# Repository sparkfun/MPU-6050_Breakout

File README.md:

Triple Axis Accelerometer & Gyro Breakout - MPU-6050
====================================================
[  
*Triple Axis Accelerometer & Gyro Breakout-MPU-6050 (SEN-11028)*](https://www.sparkfun.com/products/11028)

The MPU-6050 combines a 3-axis MEMS gyroscope and 3-axis accelerometer onto a single IC. Our breakout board
allows I2C access for the data from these sensors. 

Repository Contents
-------------------
* **/Hardware** - All Eagle design files (.brd, .sch)
* **/Production** - Test bed files and production panel files

License Information
-------------------
The hardware is released under [Creative Commons Share-alike 3.0](http://creativecommons.org/licenses/by-sa/3.0/).

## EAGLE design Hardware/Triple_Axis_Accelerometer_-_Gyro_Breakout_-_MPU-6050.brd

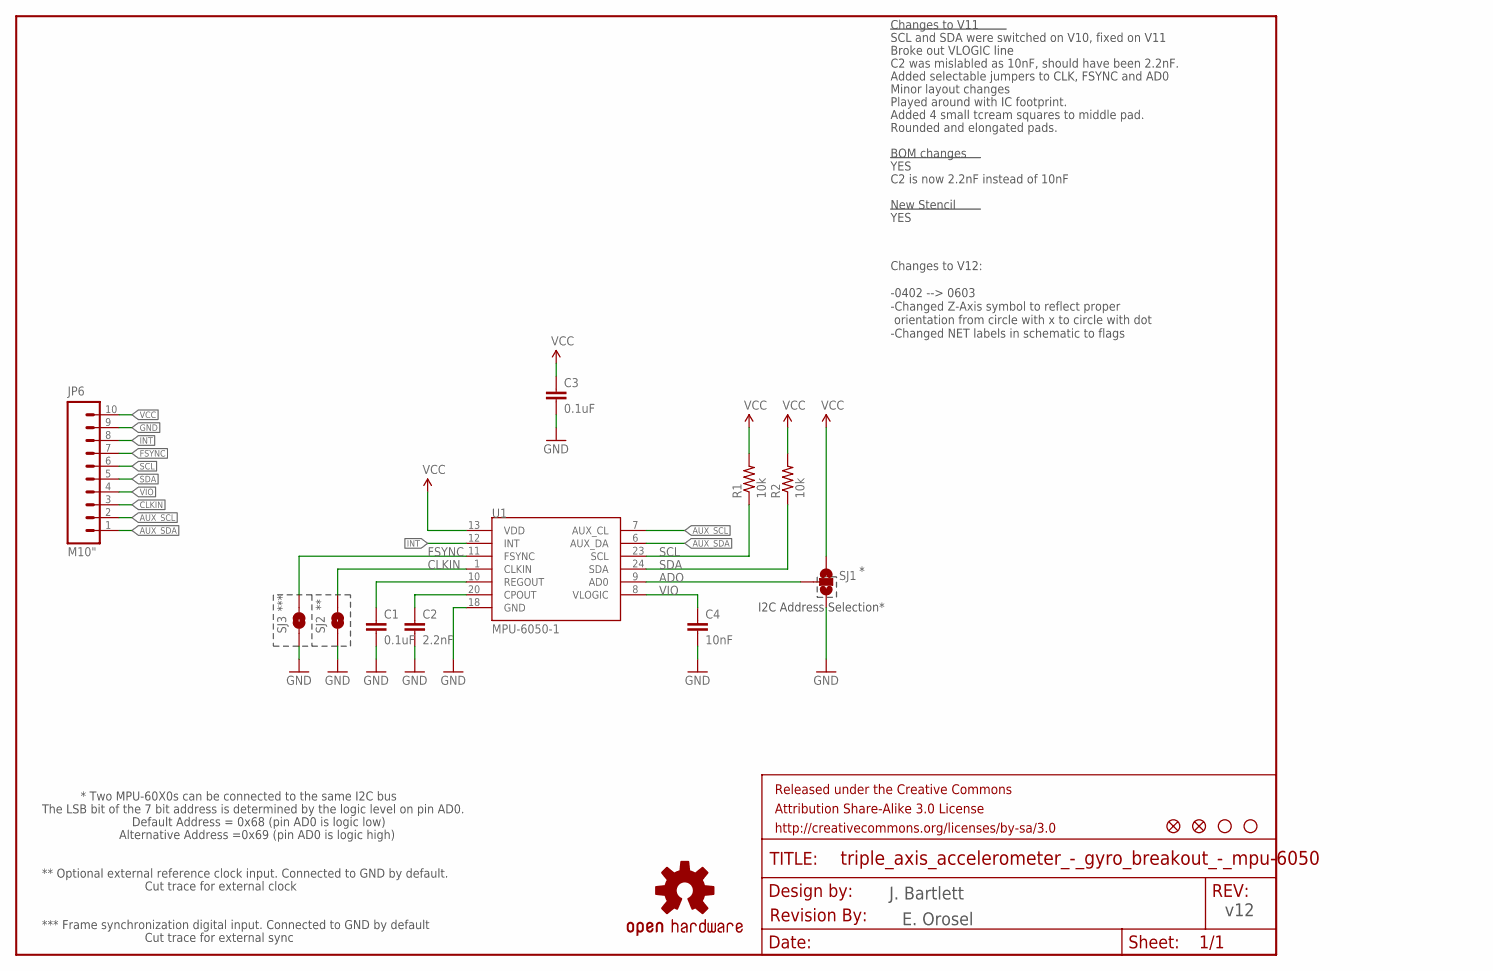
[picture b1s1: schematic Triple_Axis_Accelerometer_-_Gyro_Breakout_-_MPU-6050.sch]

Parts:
C1, C3: 0.1uF; 0603-CAP
C2: 2.2nF; 0603-CAP
C4: 10nF; 0603-CAP
FRAME1: FRAME-LETTER; CREATIVE_COMMONS
JP2, JP5: FIDUCIALUFIDUCIAL; MICRO-FIDUCIAL
JP3, JP4: STAND-OFFTIGHT; STAND-OFF-TIGHT
JP6: M10"; 1X10
R1, R2: 10k; 0603-RES
SJ1: SOLDERJUMPER_2WAYPASTE2&3; SJ_3_PASTE2&3
SJ2, SJ3: SOLDERJUMPERTRACE; SJ_2S-TRACE
U1: MPU-6050-1; QFN-24-4MM2
U$1: OSHW-LOGOS; OSHW-LOGO-S
U$5: REVISION

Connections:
ADO: SJ1.2, U1.9 (AD0)
AUX_SCL: JP6.2, U1.7 (AUX_CL)
AUX_SDA: JP6.1, U1.6 (AUX_DA)
CLKIN: JP6.3, SJ2.2, U1.1 (CLKIN)
FSYNC: JP6.7, SJ3.2, U1.11 (FSYNC)
GND: C1.2, C2.2, C3.2, C4.2, JP6.9, SJ1.3, SJ2.1, SJ3.1, U1.18 (GND)
INT: JP6.8, U1.12 (INT)
unnamed: C2.1, U1.20 (CPOUT)
unnamed: C1.1, U1.10 (REGOUT)
SCL: JP6.6, R1.1, U1.23 (SCL)
SDA: JP6.5, R2.1, U1.24 (SDA)
VCC: C3.1, JP6.10, R1.2, R2.2, SJ1.1, U1.13 (VDD)
VIO: C4.1, JP6.4, U1.8 (VLOGIC)

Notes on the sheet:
J. Bartlett
I2C Address Selection*
*** Frame synchronization digital input. Connected to GND by default
***
Cut trace for external sync
* Two MPU-60X0s can be connected to the same I2C bus
Default Address = 0x68 (pin AD0 is logic low)
Alternative Address =0x69 (pin AD0 is logic high)
The LSB bit of the 7 bit address is determined by the logic level on pin AD0.
** Optional external reference clock input. Connected to GND by default.
Cut trace for external clock
Changes to V11
SCL and SDA were switched on V10, fixed on V11
C2 was mislabled as 10nF, should have been 2.2nF.
Broke out VLOGIC line
BOM changes
New Stencil
YES
C2 is now 2.2nF instead of 10nF
Minor layout changes
Added selectable jumpers to CLK, FSYNC and AD0
Played around with IC footprint.
Changes to V12: -0402 --> 0603 -Changed Z-Axis symbol to reflect proper orientation from circle with x to circle with dot -Changed NET labels in schematic to flags
E. Orosel
v12
Added 4 small tcream squares to middle pad.
Rounded and elongated pads.

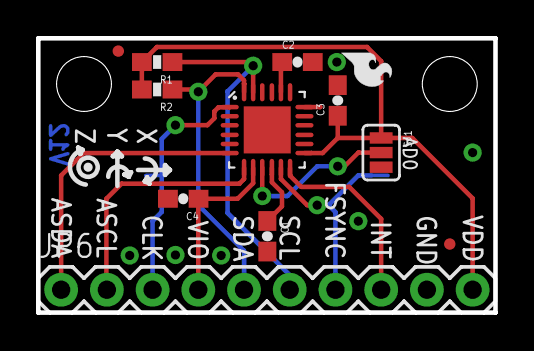
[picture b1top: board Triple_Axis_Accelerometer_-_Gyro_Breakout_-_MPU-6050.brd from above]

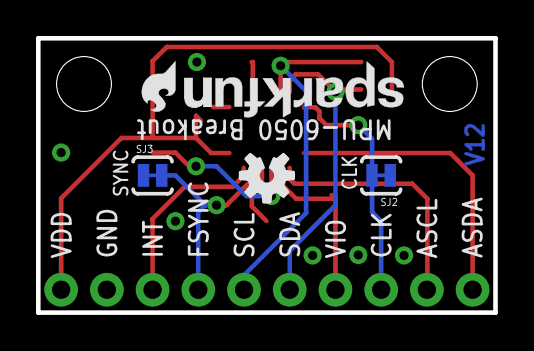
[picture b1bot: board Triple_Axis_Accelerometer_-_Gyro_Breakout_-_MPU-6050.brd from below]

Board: 2 copper layers, 25.4 x 15.2 mm, 21 parts (5 on the bottom side), 13 nets.

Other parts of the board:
U$2, U$3: SFE-LOGO-FLAME
U$4: SFE-NEW-WEB

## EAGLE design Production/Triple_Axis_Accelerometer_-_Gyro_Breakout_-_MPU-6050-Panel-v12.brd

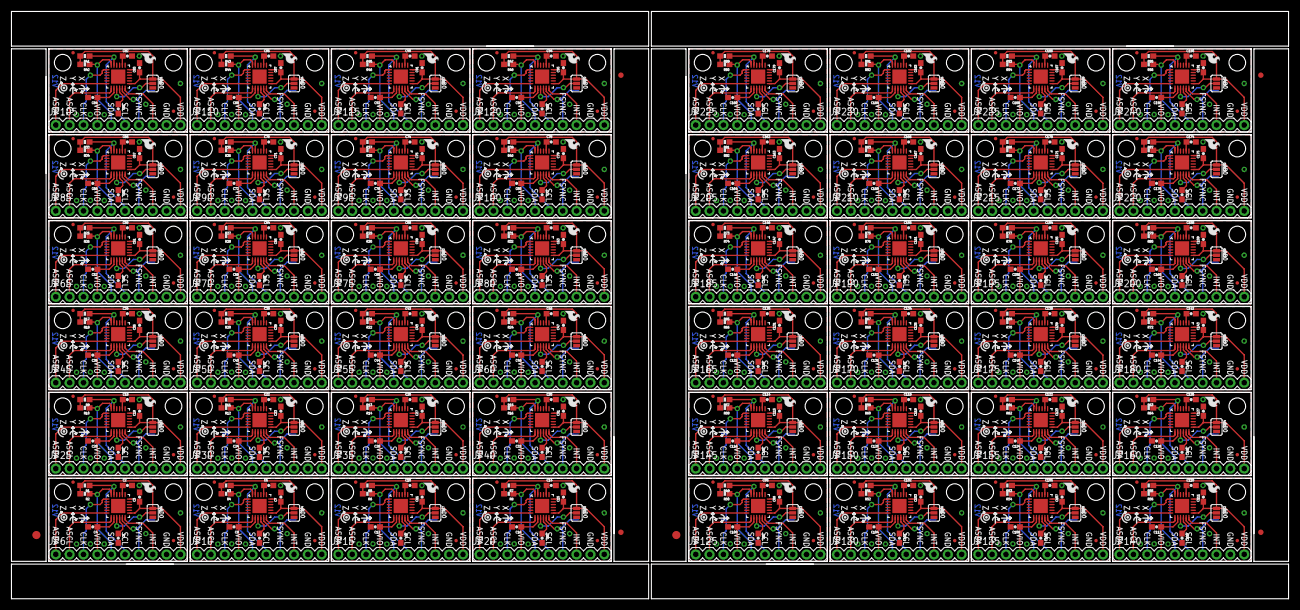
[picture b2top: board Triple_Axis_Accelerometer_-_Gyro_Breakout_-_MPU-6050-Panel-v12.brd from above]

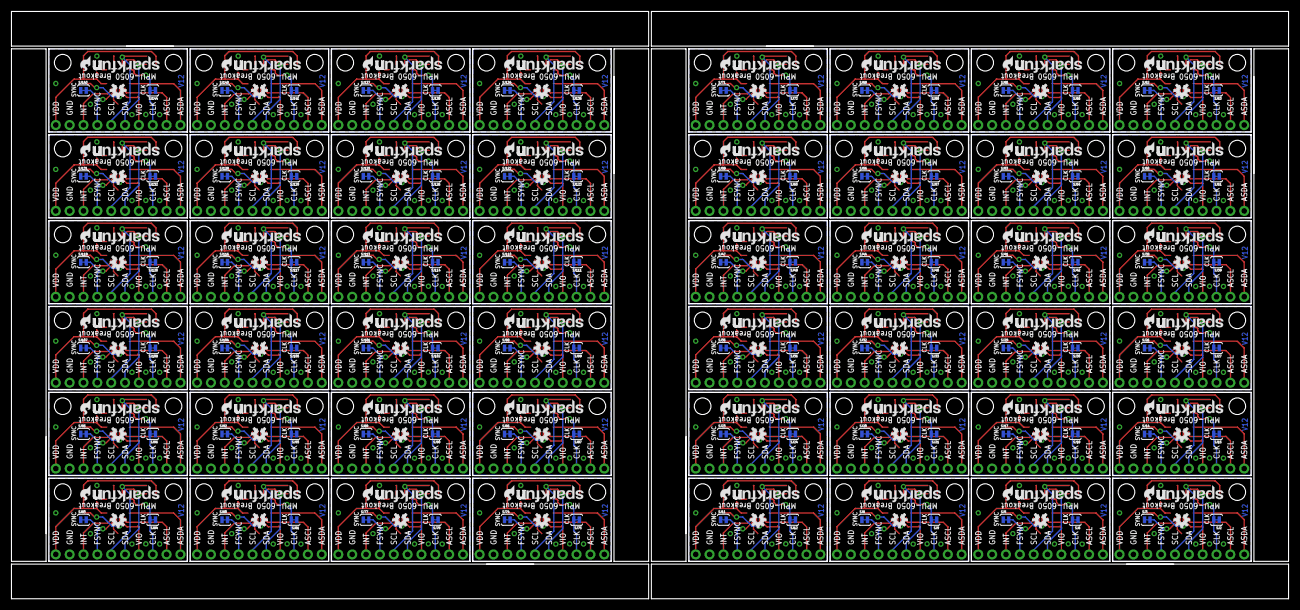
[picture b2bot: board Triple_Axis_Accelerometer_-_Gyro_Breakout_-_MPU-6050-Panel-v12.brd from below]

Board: 2 copper layers, 234.2 x 107.7 mm, 918 parts (240 on the bottom side), 624 nets.

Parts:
C1, C3, C5, C7, C9, C11, C13, C15, C17, C19, C21, C23, C25, C27, C29, C31, C33, C35, C37, C39, C41, C43, C45, C47, C49, C51, C53, C55, C57, C59, C61, C63, C65, C67, C69, C71, C73, C75, C77, C79, C81, C83, C85, C87, C89, C91, C93, C95, C97, C99, C101, C103, C105, C107, C109, C111, C113, C115, C117, C119, C121, C123, C125, C127, C129, C131, C133, C135, C137, C139, C141, C143, C145, C147, C149, C151, C153, C155, C157, C159, C161, C163, C165, C167, C169, C171, C173, C175, C177, C179, C181, C183, C185, C187, C189, C191: 0.1uF; 0603-CAP
C2, C6, C10, C14, C18, C22, C26, C30, C34, C38, C42, C46, C50, C54, C58, C62, C66, C70, C74, C78, C82, C86, C90, C94, C98, C102, C106, C110, C114, C118, C122, C126, C130, C134, C138, C142, C146, C150, C154, C158, C162, C166, C170, C174, C178, C182, C186, C190: 2.2nF; 0603-CAP
C4, C8, C12, C16, C20, C24, C28, C32, C36, C40, C44, C48, C52, C56, C60, C64, C68, C72, C76, C80, C84, C88, C92, C96, C100, C104, C108, C112, C116, C120, C124, C128, C132, C136, C140, C144, C148, C152, C156, C160, C164, C168, C172, C176, C180, C184, C188, C192: 10nF; 0603-CAP
E$1, E$6: FIDUCIAL-1.5X3
E$2, E$3, E$4, E$5: FIDUCIAL-1X2
JP1, JP3, JP4, JP7, JP11, JP12, JP16, JP17, JP21, JP22, JP26, JP27, JP31, JP32, JP36, JP37, JP41, JP42, JP46, JP47, JP51, JP52, JP56, JP57, JP61, JP62, JP66, JP67, JP71, JP72, JP76, JP77, JP81, JP82, JP86, JP87, JP91, JP92, JP96, JP97, JP101, JP102, JP106, JP107, JP111, JP112, JP116, JP117, JP121, JP122, JP126, JP127, JP131, JP132, JP136, JP137, JP141, JP142, JP146, JP147, JP151, JP152, JP156, JP157, JP161, JP162, JP166, JP167, JP171, JP172, JP176, JP177, JP181, JP182, JP186, JP187, JP191, JP192, JP196, JP197, JP201, JP202, JP206, JP207, JP211, JP212, JP216, JP217, JP221, JP222, JP226, JP227, JP231, JP232, JP236, JP237: STAND-OFFTIGHT; STAND-OFF-TIGHT
JP2, JP5, JP8, JP9, JP13, JP14, JP18, JP19, JP23, JP24, JP28, JP29, JP33, JP34, JP38, JP39, JP43, JP44, JP48, JP49, JP53, JP54, JP58, JP59, JP63, JP64, JP68, JP69, JP73, JP74, JP78, JP79, JP83, JP84, JP88, JP89, JP93, JP94, JP98, JP99, JP103, JP104, JP108, JP109, JP113, JP114, JP118, JP119, JP123, JP124, JP128, JP129, JP133, JP134, JP138, JP139, JP143, JP144, JP148, JP149, JP153, JP154, JP158, JP159, JP163, JP164, JP168, JP169, JP173, JP174, JP178, JP179, JP183, JP184, JP188, JP189, JP193, JP194, JP198, JP199, JP203, JP204, JP208, JP209, JP213, JP214, JP218, JP219, JP223, JP224, JP228, JP229, JP233, JP234, JP238, JP239: FIDUCIALUFIDUCIAL; MICRO-FIDUCIAL
JP6, JP10, JP15, JP20, JP25, JP30, JP35, JP40, JP45, JP50, JP55, JP60, JP65, JP70, JP75, JP80, JP85, JP90, JP95, JP100, JP105, JP110, JP115, JP120, JP125, JP130, JP135, JP140, JP145, JP150, JP155, JP160, JP165, JP170, JP175, JP180, JP185, JP190, JP195, JP200, JP205, JP210, JP215, JP220, JP225, JP230, JP235, JP240: M10"; 1X10
R1, R2, R3, R4, R5, R6, R7, R8, R9, R10, R11, R12, R13, R14, R15, R16, R17, R18, R19, R20, R21, R22, R23, R24, R25, R26, R27, R28, R29, R30, R31, R32, R33, R34, R35, R36, R37, R38, R39, R40, R41, R42, R43, R44, R45, R46, R47, R48, R49, R50, R51, R52, R53, R54, R55, R56, R57, R58, R59, R60, R61, R62, R63, R64, R65, R66, R67, R68, R69, R70, R71, R72, R73, R74, R75, R76, R77, R78, R79, R80, R81, R82, R83, R84, R85, R86, R87, R88, R89, R90, R91, R92, R93, R94, R95, R96: 10k; 0603-RES
SJ1, SJ4, SJ7, SJ10, SJ13, SJ16, SJ19, SJ22, SJ25, SJ28, SJ31, SJ34, SJ37, SJ40, SJ43, SJ46, SJ49, SJ52, SJ55, SJ58, SJ61, SJ64, SJ67, SJ70, SJ73, SJ76, SJ79, SJ82, SJ85, SJ88, SJ91, SJ94, SJ97, SJ100, SJ103, SJ106, SJ109, SJ112, SJ115, SJ118, SJ121, SJ124, SJ127, SJ130, SJ133, SJ136, SJ139, SJ142: SJ_3_PASTE2&3
SJ2, SJ3, SJ5, SJ6, SJ8, SJ9, SJ11, SJ12, SJ14, SJ15, SJ17, SJ18, SJ20, SJ21, SJ23, SJ24, SJ26, SJ27, SJ29, SJ30, SJ32, SJ33, SJ35, SJ36, SJ38, SJ39, SJ41, SJ42, SJ44, SJ45, SJ47, SJ48, SJ50, SJ51, SJ53, SJ54, SJ56, SJ57, SJ59, SJ60, SJ62, SJ63, SJ65, SJ66, SJ68, SJ69, SJ71, SJ72, SJ74, SJ75, SJ77, SJ78, SJ80, SJ81, SJ83, SJ84, SJ86, SJ87, SJ89, SJ90, SJ92, SJ93, SJ95, SJ96, SJ98, SJ99, SJ101, SJ102, SJ104, SJ105, SJ107, SJ108, SJ110, SJ111, SJ113, SJ114, SJ116, SJ117, SJ119, SJ120, SJ122, SJ123, SJ125, SJ126, SJ128, SJ129, SJ131, SJ132, SJ134, SJ135, SJ137, SJ138, SJ140, SJ141, SJ143, SJ144: SJ_2S-TRACE
U1, U2, U3, U4, U5, U6, U7, U8, U9, U10, U11, U12, U13, U14, U15, U16, U17, U18, U19, U20, U21, U22, U23, U24, U25, U26, U27, U28, U29, U30, U31, U32, U33, U34, U35, U36, U37, U38, U39, U40, U41, U42, U43, U44, U45, U46, U47, U48: MPU-6050-1; QFN-24-4MM2
U$1, U$6, U$10, U$14, U$18, U$22, U$26, U$30, U$34, U$38, U$42, U$46, U$50, U$54, U$58, U$62, U$66, U$70, U$74, U$78, U$82, U$86, U$90, U$94, U$98, U$102, U$106, U$110, U$114, U$118, U$122, U$126, U$130, U$134, U$138, U$142, U$146, U$150, U$154, U$158, U$162, U$166, U$170, U$174, U$178, U$182, U$186, U$190: OSHW-LOGOS; OSHW-LOGO-S
U$2, U$3, U$5, U$7, U$9, U$11, U$13, U$15, U$17, U$19, U$21, U$23, U$25, U$27, U$29, U$31, U$33, U$35, U$37, U$39, U$41, U$43, U$45, U$47, U$49, U$51, U$53, U$55, U$57, U$59, U$61, U$63, U$65, U$67, U$69, U$71, U$73, U$75, U$77, U$79, U$81, U$83, U$85, U$87, U$89, U$91, U$93, U$95, U$97, U$99, U$101, U$103, U$105, U$107, U$109, U$111, U$113, U$115, U$117, U$119, U$121, U$123, U$125, U$127, U$129, U$131, U$133, U$135, U$137, U$139, U$141, U$143, U$145, U$147, U$149, U$151, U$153, U$155, U$157, U$159, U$161, U$163, U$165, U$167, U$169, U$171, U$173, U$175, U$177, U$179, U$181, U$183, U$185, U$187, U$189, U$191: SFE-LOGO-FLAME
U$4, U$8, U$12, U$16, U$20, U$24, U$28, U$32, U$36, U$40, U$44, U$48, U$52, U$56, U$60, U$64, U$68, U$72, U$76, U$80, U$84, U$88, U$92, U$96, U$100, U$104, U$108, U$112, U$116, U$120, U$124, U$128, U$132, U$136, U$140, U$144, U$148, U$152, U$156, U$160, U$164, U$168, U$172, U$176, U$180, U$184, U$188, U$192: SFE-NEW-WEB

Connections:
ADO: SJ1.2, U1.9
ADO1: SJ4.2, U2.9
ADO2: SJ7.2, U3.9
ADO3: SJ10.2, U4.9
ADO4: SJ13.2, U5.9
ADO5: SJ16.2, U6.9
ADO6: SJ19.2, U7.9
ADO7: SJ22.2, U8.9
ADO8: SJ25.2, U9.9
ADO9: SJ28.2, U10.9
ADO10: SJ31.2, U11.9
ADO11: SJ34.2, U12.9
ADO12: SJ37.2, U13.9
ADO13: SJ40.2, U14.9
ADO14: SJ43.2, U15.9
ADO15: SJ46.2, U16.9
ADO16: SJ49.2, U17.9
ADO17: SJ52.2, U18.9
ADO18: SJ55.2, U19.9
ADO19: SJ58.2, U20.9
ADO20: SJ61.2, U21.9
ADO21: SJ64.2, U22.9
ADO22: SJ67.2, U23.9
ADO23: SJ70.2, U24.9
ADO24: SJ73.2, U25.9
ADO25: SJ76.2, U26.9
ADO26: SJ79.2, U27.9
ADO27: SJ82.2, U28.9
ADO28: SJ85.2, U29.9
ADO29: SJ88.2, U30.9
ADO30: SJ91.2, U31.9
ADO31: SJ94.2, U32.9
ADO32: SJ97.2, U33.9
ADO33: SJ100.2, U34.9
ADO34: SJ103.2, U35.9
ADO35: SJ106.2, U36.9
ADO36: SJ109.2, U37.9
ADO37: SJ112.2, U38.9
ADO38: SJ115.2, U39.9
ADO39: SJ118.2, U40.9
ADO40: SJ121.2, U41.9
ADO41: SJ124.2, U42.9
ADO42: SJ127.2, U43.9
ADO43: SJ130.2, U44.9
ADO44: SJ133.2, U45.9
ADO45: SJ136.2, U46.9
ADO46: SJ139.2, U47.9
ADO47: SJ142.2, U48.9
AUX_SCL: JP6.2, U1.7
AUX_SCL1: JP10.2, U2.7
AUX_SCL2: JP15.2, U3.7
AUX_SCL3: JP20.2, U4.7
AUX_SCL4: JP25.2, U5.7
AUX_SCL5: JP30.2, U6.7
AUX_SCL6: JP35.2, U7.7
AUX_SCL7: JP40.2, U8.7
AUX_SCL8: JP45.2, U9.7
AUX_SCL9: JP50.2, U10.7
AUX_SCL10: JP55.2, U11.7
AUX_SCL11: JP60.2, U12.7
AUX_SCL12: JP65.2, U13.7
AUX_SCL13: JP70.2, U14.7
AUX_SCL14: JP75.2, U15.7
AUX_SCL15: JP80.2, U16.7
AUX_SCL16: JP85.2, U17.7
AUX_SCL17: JP90.2, U18.7
AUX_SCL18: JP95.2, U19.7
AUX_SCL19: JP100.2, U20.7
AUX_SCL20: JP105.2, U21.7
AUX_SCL21: JP110.2, U22.7
AUX_SCL22: JP115.2, U23.7
AUX_SCL23: JP120.2, U24.7
AUX_SCL24: JP125.2, U25.7
AUX_SCL25: JP130.2, U26.7
AUX_SCL26: JP135.2, U27.7
AUX_SCL27: JP140.2, U28.7
AUX_SCL28: JP145.2, U29.7
AUX_SCL29: JP150.2, U30.7
AUX_SCL30: JP155.2, U31.7
AUX_SCL31: JP160.2, U32.7
AUX_SCL32: JP165.2, U33.7
AUX_SCL33: JP170.2, U34.7
AUX_SCL34: JP175.2, U35.7
AUX_SCL35: JP180.2, U36.7
AUX_SCL36: JP185.2, U37.7
AUX_SCL37: JP190.2, U38.7
AUX_SCL38: JP195.2, U39.7
AUX_SCL39: JP200.2, U40.7
AUX_SCL40: JP205.2, U41.7
AUX_SCL41: JP210.2, U42.7
AUX_SCL42: JP215.2, U43.7
AUX_SCL43: JP220.2, U44.7
AUX_SCL44: JP225.2, U45.7
AUX_SCL45: JP230.2, U46.7
AUX_SCL46: JP235.2, U47.7
AUX_SCL47: JP240.2, U48.7
AUX_SDA: JP6.1, U1.6
AUX_SDA1: JP10.1, U2.6
AUX_SDA2: JP15.1, U3.6
AUX_SDA3: JP20.1, U4.6
AUX_SDA4: JP25.1, U5.6
AUX_SDA5: JP30.1, U6.6
AUX_SDA6: JP35.1, U7.6
AUX_SDA7: JP40.1, U8.6
AUX_SDA8: JP45.1, U9.6
AUX_SDA9: JP50.1, U10.6
AUX_SDA10: JP55.1, U11.6
AUX_SDA11: JP60.1, U12.6
AUX_SDA12: JP65.1, U13.6
AUX_SDA13: JP70.1, U14.6
AUX_SDA14: JP75.1, U15.6
AUX_SDA15: JP80.1, U16.6
AUX_SDA16: JP85.1, U17.6
AUX_SDA17: JP90.1, U18.6
AUX_SDA18: JP95.1, U19.6
AUX_SDA19: JP100.1, U20.6
AUX_SDA20: JP105.1, U21.6
AUX_SDA21: JP110.1, U22.6
AUX_SDA22: JP115.1, U23.6
AUX_SDA23: JP120.1, U24.6
AUX_SDA24: JP125.1, U25.6
AUX_SDA25: JP130.1, U26.6
AUX_SDA26: JP135.1, U27.6
AUX_SDA27: JP140.1, U28.6
AUX_SDA28: JP145.1, U29.6
AUX_SDA29: JP150.1, U30.6
AUX_SDA30: JP155.1, U31.6
AUX_SDA31: JP160.1, U32.6
AUX_SDA32: JP165.1, U33.6
AUX_SDA33: JP170.1, U34.6
AUX_SDA34: JP175.1, U35.6
AUX_SDA35: JP180.1, U36.6
AUX_SDA36: JP185.1, U37.6
AUX_SDA37: JP190.1, U38.6
AUX_SDA38: JP195.1, U39.6
AUX_SDA39: JP200.1, U40.6
AUX_SDA40: JP205.1, U41.6
AUX_SDA41: JP210.1, U42.6
AUX_SDA42: JP215.1, U43.6
AUX_SDA43: JP220.1, U44.6
AUX_SDA44: JP225.1, U45.6
AUX_SDA45: JP230.1, U46.6
AUX_SDA46: JP235.1, U47.6
AUX_SDA47: JP240.1, U48.6
CLKIN: JP6.3, SJ2.2, U1.1
CLKIN1: JP10.3, SJ6.2, U2.1
CLKIN2: JP15.3, SJ9.2, U3.1
CLKIN3: JP20.3, SJ12.2, U4.1
CLKIN4: JP25.3, SJ15.2, U5.1
CLKIN5: JP30.3, SJ18.2, U6.1
CLKIN6: JP35.3, SJ21.2, U7.1
CLKIN7: JP40.3, SJ24.2, U8.1
CLKIN8: JP45.3, SJ27.2, U9.1
CLKIN9: JP50.3, SJ30.2, U10.1
CLKIN10: JP55.3, SJ33.2, U11.1
CLKIN11: JP60.3, SJ36.2, U12.1
CLKIN12: JP65.3, SJ39.2, U13.1
CLKIN13: JP70.3, SJ42.2, U14.1
CLKIN14: JP75.3, SJ45.2, U15.1
CLKIN15: JP80.3, SJ48.2, U16.1
CLKIN16: JP85.3, SJ51.2, U17.1
CLKIN17: JP90.3, SJ54.2, U18.1
CLKIN18: JP95.3, SJ57.2, U19.1
CLKIN19: JP100.3, SJ60.2, U20.1
CLKIN20: JP105.3, SJ63.2, U21.1
CLKIN21: JP110.3, SJ66.2, U22.1
CLKIN22: JP115.3, SJ69.2, U23.1
CLKIN23: JP120.3, SJ72.2, U24.1
CLKIN24: JP125.3, SJ75.2, U25.1
CLKIN25: JP130.3, SJ78.2, U26.1
CLKIN26: JP135.3, SJ81.2, U27.1
CLKIN27: JP140.3, SJ84.2, U28.1
CLKIN28: JP145.3, SJ87.2, U29.1
CLKIN29: JP150.3, SJ90.2, U30.1
CLKIN30: JP155.3, SJ93.2, U31.1
CLKIN31: JP160.3, SJ96.2, U32.1
CLKIN32: JP165.3, SJ99.2, U33.1
CLKIN33: JP170.3, SJ102.2, U34.1
CLKIN34: JP175.3, SJ105.2, U35.1
CLKIN35: JP180.3, SJ108.2, U36.1
CLKIN36: JP185.3, SJ111.2, U37.1
CLKIN37: JP190.3, SJ114.2, U38.1
CLKIN38: JP195.3, SJ117.2, U39.1
CLKIN39: JP200.3, SJ120.2, U40.1
CLKIN40: JP205.3, SJ123.2, U41.1
CLKIN41: JP210.3, SJ126.2, U42.1
CLKIN42: JP215.3, SJ129.2, U43.1
CLKIN43: JP220.3, SJ132.2, U44.1
CLKIN44: JP225.3, SJ135.2, U45.1
CLKIN45: JP230.3, SJ138.2, U46.1
CLKIN46: JP235.3, SJ141.2, U47.1
CLKIN47: JP240.3, SJ144.2, U48.1
FSYNC: JP6.7, SJ3.2, U1.11
FSYNC1: JP10.7, SJ5.2, U2.11
FSYNC2: JP15.7, SJ8.2, U3.11
FSYNC3: JP20.7, SJ11.2, U4.11
FSYNC4: JP25.7, SJ14.2, U5.11
FSYNC5: JP30.7, SJ17.2, U6.11
FSYNC6: JP35.7, SJ20.2, U7.11
FSYNC7: JP40.7, SJ23.2, U8.11
FSYNC8: JP45.7, SJ26.2, U9.11
FSYNC9: JP50.7, SJ29.2, U10.11
FSYNC10: JP55.7, SJ32.2, U11.11
FSYNC11: JP60.7, SJ35.2, U12.11
FSYNC12: JP65.7, SJ38.2, U13.11
FSYNC13: JP70.7, SJ41.2, U14.11
FSYNC14: JP75.7, SJ44.2, U15.11
FSYNC15: JP80.7, SJ47.2, U16.11
FSYNC16: JP85.7, SJ50.2, U17.11
FSYNC17: JP90.7, SJ53.2, U18.11
FSYNC18: JP95.7, SJ56.2, U19.11
FSYNC19: JP100.7, SJ59.2, U20.11
FSYNC20: JP105.7, SJ62.2, U21.11
FSYNC21: JP110.7, SJ65.2, U22.11
FSYNC22: JP115.7, SJ68.2, U23.11
FSYNC23: JP120.7, SJ71.2, U24.11
FSYNC24: JP125.7, SJ74.2, U25.11
FSYNC25: JP130.7, SJ77.2, U26.11
FSYNC26: JP135.7, SJ80.2, U27.11
FSYNC27: JP140.7, SJ83.2, U28.11
FSYNC28: JP145.7, SJ86.2, U29.11
FSYNC29: JP150.7, SJ89.2, U30.11
FSYNC30: JP155.7, SJ92.2, U31.11
FSYNC31: JP160.7, SJ95.2, U32.11
FSYNC32: JP165.7, SJ98.2, U33.11
FSYNC33: JP170.7, SJ101.2, U34.11
FSYNC34: JP175.7, SJ104.2, U35.11
FSYNC35: JP180.7, SJ107.2, U36.11
FSYNC36: JP185.7, SJ110.2, U37.11
FSYNC37: JP190.7, SJ113.2, U38.11
FSYNC38: JP195.7, SJ116.2, U39.11
FSYNC39: JP200.7, SJ119.2, U40.11
FSYNC40: JP205.7, SJ122.2, U41.11
FSYNC41: JP210.7, SJ125.2, U42.11
FSYNC42: JP215.7, SJ128.2, U43.11
FSYNC43: JP220.7, SJ131.2, U44.11
FSYNC44: JP225.7, SJ134.2, U45.11
FSYNC45: JP230.7, SJ137.2, U46.11
FSYNC46: JP235.7, SJ140.2, U47.11
FSYNC47: JP240.7, SJ143.2, U48.11
GND: C1.2, C2.2, C3.2, C4.2, JP6.9, SJ1.3, SJ2.1, SJ3.1, U1.18
GND1: C5.2, C6.2, C7.2, C8.2, JP10.9, SJ4.3, SJ5.1, SJ6.1, U2.18
GND2: C9.2, C10.2, C11.2, C12.2, JP15.9, SJ7.3, SJ8.1, SJ9.1, U3.18
GND3: C13.2, C14.2, C15.2, C16.2, JP20.9, SJ10.3, SJ11.1, SJ12.1, U4.18
GND4: C17.2, C18.2, C19.2, C20.2, JP25.9, SJ13.3, SJ14.1, SJ15.1, U5.18
GND5: C21.2, C22.2, C23.2, C24.2, JP30.9, SJ16.3, SJ17.1, SJ18.1, U6.18
GND6: C25.2, C26.2, C27.2, C28.2, JP35.9, SJ19.3, SJ20.1, SJ21.1, U7.18
GND7: C29.2, C30.2, C31.2, C32.2, JP40.9, SJ22.3, SJ23.1, SJ24.1, U8.18
GND8: C33.2, C34.2, C35.2, C36.2, JP45.9, SJ25.3, SJ26.1, SJ27.1, U9.18
GND9: C37.2, C38.2, C39.2, C40.2, JP50.9, SJ28.3, SJ29.1, SJ30.1, U10.18
GND10: C41.2, C42.2, C43.2, C44.2, JP55.9, SJ31.3, SJ32.1, SJ33.1, U11.18
GND11: C45.2, C46.2, C47.2, C48.2, JP60.9, SJ34.3, SJ35.1, SJ36.1, U12.18
GND12: C49.2, C50.2, C51.2, C52.2, JP65.9, SJ37.3, SJ38.1, SJ39.1, U13.18
GND13: C53.2, C54.2, C55.2, C56.2, JP70.9, SJ40.3, SJ41.1, SJ42.1, U14.18
GND14: C57.2, C58.2, C59.2, C60.2, JP75.9, SJ43.3, SJ44.1, SJ45.1, U15.18
GND15: C61.2, C62.2, C63.2, C64.2, JP80.9, SJ46.3, SJ47.1, SJ48.1, U16.18
GND16: C65.2, C66.2, C67.2, C68.2, JP85.9, SJ49.3, SJ50.1, SJ51.1, U17.18
GND17: C69.2, C70.2, C71.2, C72.2, JP90.9, SJ52.3, SJ53.1, SJ54.1, U18.18
GND18: C73.2, C74.2, C75.2, C76.2, JP95.9, SJ55.3, SJ56.1, SJ57.1, U19.18
GND19: C77.2, C78.2, C79.2, C80.2, JP100.9, SJ58.3, SJ59.1, SJ60.1, U20.18
GND20: C81.2, C82.2, C83.2, C84.2, JP105.9, SJ61.3, SJ62.1, SJ63.1, U21.18
GND21: C85.2, C86.2, C87.2, C88.2, JP110.9, SJ64.3, SJ65.1, SJ66.1, U22.18
GND22: C89.2, C90.2, C91.2, C92.2, JP115.9, SJ67.3, SJ68.1, SJ69.1, U23.18
GND23: C93.2, C94.2, C95.2, C96.2, JP120.9, SJ70.3, SJ71.1, SJ72.1, U24.18
GND24: C97.2, C98.2, C99.2, C100.2, JP125.9, SJ73.3, SJ74.1, SJ75.1, U25.18
GND25: C101.2, C102.2, C103.2, C104.2, JP130.9, SJ76.3, SJ77.1, SJ78.1, U26.18
GND26: C105.2, C106.2, C107.2, C108.2, JP135.9, SJ79.3, SJ80.1, SJ81.1, U27.18
GND27: C109.2, C110.2, C111.2, C112.2, JP140.9, SJ82.3, SJ83.1, SJ84.1, U28.18
GND28: C113.2, C114.2, C115.2, C116.2, JP145.9, SJ85.3, SJ86.1, SJ87.1, U29.18
GND29: C117.2, C118.2, C119.2, C120.2, JP150.9, SJ88.3, SJ89.1, SJ90.1, U30.18
GND30: C121.2, C122.2, C123.2, C124.2, JP155.9, SJ91.3, SJ92.1, SJ93.1, U31.18
GND31: C125.2, C126.2, C127.2, C128.2, JP160.9, SJ94.3, SJ95.1, SJ96.1, U32.18
GND32: C129.2, C130.2, C131.2, C132.2, JP165.9, SJ97.3, SJ98.1, SJ99.1, U33.18
GND33: C133.2, C134.2, C135.2, C136.2, JP170.9, SJ100.3, SJ101.1, SJ102.1, U34.18
GND34: C137.2, C138.2, C139.2, C140.2, JP175.9, SJ103.3, SJ104.1, SJ105.1, U35.18
GND35: C141.2, C142.2, C143.2, C144.2, JP180.9, SJ106.3, SJ107.1, SJ108.1, U36.18
GND36: C145.2, C146.2, C147.2, C148.2, JP185.9, SJ109.3, SJ110.1, SJ111.1, U37.18
GND37: C149.2, C150.2, C151.2, C152.2, JP190.9, SJ112.3, SJ113.1, SJ114.1, U38.18
GND38: C153.2, C154.2, C155.2, C156.2, JP195.9, SJ115.3, SJ116.1, SJ117.1, U39.18
GND39: C157.2, C158.2, C159.2, C160.2, JP200.9, SJ118.3, SJ119.1, SJ120.1, U40.18
GND40: C161.2, C162.2, C163.2, C164.2, JP205.9, SJ121.3, SJ122.1, SJ123.1, U41.18
GND41: C165.2, C166.2, C167.2, C168.2, JP210.9, SJ124.3, SJ125.1, SJ126.1, U42.18
GND42: C169.2, C170.2, C171.2, C172.2, JP215.9, SJ127.3, SJ128.1, SJ129.1, U43.18
GND43: C173.2, C174.2, C175.2, C176.2, JP220.9, SJ130.3, SJ131.1, SJ132.1, U44.18
GND44: C177.2, C178.2, C179.2, C180.2, JP225.9, SJ133.3, SJ134.1, SJ135.1, U45.18
GND45: C181.2, C182.2, C183.2, C184.2, JP230.9, SJ136.3, SJ137.1, SJ138.1, U46.18
GND46: C185.2, C186.2, C187.2, C188.2, JP235.9, SJ139.3, SJ140.1, SJ141.1, U47.18
GND47: C189.2, C190.2, C191.2, C192.2, JP240.9, SJ142.3, SJ143.1, SJ144.1, U48.18
INT: JP6.8, U1.12
INT1: JP10.8, U2.12
INT2: JP15.8, U3.12
INT3: JP20.8, U4.12
INT4: JP25.8, U5.12
INT5: JP30.8, U6.12
INT6: JP35.8, U7.12
INT7: JP40.8, U8.12
INT8: JP45.8, U9.12
INT9: JP50.8, U10.12
INT10: JP55.8, U11.12
INT11: JP60.8, U12.12
INT12: JP65.8, U13.12
INT13: JP70.8, U14.12
INT14: JP75.8, U15.12
INT15: JP80.8, U16.12
INT16: JP85.8, U17.12
INT17: JP90.8, U18.12
INT18: JP95.8, U19.12
INT19: JP100.8, U20.12
INT20: JP105.8, U21.12
INT21: JP110.8, U22.12
INT22: JP115.8, U23.12
INT23: JP120.8, U24.12
INT24: JP125.8, U25.12
INT25: JP130.8, U26.12
INT26: JP135.8, U27.12
INT27: JP140.8, U28.12
INT28: JP145.8, U29.12
INT29: JP150.8, U30.12
INT30: JP155.8, U31.12
INT31: JP160.8, U32.12
INT32: JP165.8, U33.12
INT33: JP170.8, U34.12
INT34: JP175.8, U35.12
INT35: JP180.8, U36.12
INT36: JP185.8, U37.12
INT37: JP190.8, U38.12
INT38: JP195.8, U39.12
INT39: JP200.8, U40.12
INT40: JP205.8, U41.12
INT41: JP210.8, U42.12
INT42: JP215.8, U43.12
INT43: JP220.8, U44.12
INT44: JP225.8, U45.12
INT45: JP230.8, U46.12
INT46: JP235.8, U47.12
INT47: JP240.8, U48.12
unnamed: C6.1, U2.20
unnamed: C5.1, U2.10
unnamed: C2.1, U1.20
unnamed: C10.1, U3.20
unnamed: C1.1, U1.10
unnamed: C9.1, U3.10
unnamed: C14.1, U4.20
unnamed: C13.1, U4.10
unnamed: C18.1, U5.20
unnamed: C17.1, U5.10
unnamed: C22.1, U6.20
unnamed: C21.1, U6.10
unnamed: C26.1, U7.20
unnamed: C25.1, U7.10
unnamed: C30.1, U8.20
unnamed: C29.1, U8.10
unnamed: C34.1, U9.20
unnamed: C33.1, U9.10
unnamed: C38.1, U10.20
unnamed: C37.1, U10.10
unnamed: C42.1, U11.20
unnamed: C41.1, U11.10
unnamed: C46.1, U12.20
unnamed: C45.1, U12.10
unnamed: C50.1, U13.20
unnamed: C49.1, U13.10
unnamed: C54.1, U14.20
unnamed: C53.1, U14.10
unnamed: C58.1, U15.20
unnamed: C57.1, U15.10
unnamed: C62.1, U16.20
unnamed: C61.1, U16.10
unnamed: C66.1, U17.20
unnamed: C65.1, U17.10
unnamed: C70.1, U18.20
unnamed: C69.1, U18.10
unnamed: C74.1, U19.20
unnamed: C73.1, U19.10
unnamed: C78.1, U20.20
unnamed: C77.1, U20.10
unnamed: C82.1, U21.20
unnamed: C81.1, U21.10
unnamed: C86.1, U22.20
unnamed: C85.1, U22.10
unnamed: C90.1, U23.20
unnamed: C89.1, U23.10
unnamed: C94.1, U24.20
unnamed: C93.1, U24.10
unnamed: C98.1, U25.20
unnamed: C97.1, U25.10
unnamed: C102.1, U26.20
unnamed: C101.1, U26.10
unnamed: C106.1, U27.20
unnamed: C105.1, U27.10
unnamed: C110.1, U28.20
unnamed: C109.1, U28.10
unnamed: C114.1, U29.20
unnamed: C113.1, U29.10
unnamed: C118.1, U30.20
unnamed: C117.1, U30.10
unnamed: C122.1, U31.20
unnamed: C121.1, U31.10
unnamed: C126.1, U32.20
unnamed: C125.1, U32.10
unnamed: C130.1, U33.20
unnamed: C129.1, U33.10
unnamed: C134.1, U34.20
unnamed: C133.1, U34.10
unnamed: C138.1, U35.20
unnamed: C137.1, U35.10
unnamed: C142.1, U36.20
unnamed: C141.1, U36.10
unnamed: C146.1, U37.20
unnamed: C145.1, U37.10
unnamed: C150.1, U38.20
unnamed: C149.1, U38.10
unnamed: C154.1, U39.20
unnamed: C153.1, U39.10
unnamed: C158.1, U40.20
unnamed: C157.1, U40.10
unnamed: C162.1, U41.20
unnamed: C161.1, U41.10
unnamed: C166.1, U42.20
unnamed: C165.1, U42.10
unnamed: C170.1, U43.20
unnamed: C169.1, U43.10
unnamed: C174.1, U44.20
unnamed: C173.1, U44.10
unnamed: C178.1, U45.20
unnamed: C177.1, U45.10
unnamed: C182.1, U46.20
unnamed: C181.1, U46.10
unnamed: C186.1, U47.20
unnamed: C185.1, U47.10
unnamed: C190.1, U48.20
unnamed: C189.1, U48.10
SCL: JP6.6, R1.1, U1.23
SCL1: JP10.6, R3.1, U2.23
SCL2: JP15.6, R5.1, U3.23
SCL3: JP20.6, R7.1, U4.23
SCL4: JP25.6, R9.1, U5.23
SCL5: JP30.6, R11.1, U6.23
SCL6: JP35.6, R13.1, U7.23
SCL7: JP40.6, R15.1, U8.23
SCL8: JP45.6, R17.1, U9.23
SCL9: JP50.6, R19.1, U10.23
SCL10: JP55.6, R21.1, U11.23
SCL11: JP60.6, R23.1, U12.23
SCL12: JP65.6, R25.1, U13.23
SCL13: JP70.6, R27.1, U14.23
SCL14: JP75.6, R29.1, U15.23
SCL15: JP80.6, R31.1, U16.23
SCL16: JP85.6, R33.1, U17.23
SCL17: JP90.6, R35.1, U18.23
SCL18: JP95.6, R37.1, U19.23
SCL19: JP100.6, R39.1, U20.23
SCL20: JP105.6, R41.1, U21.23
SCL21: JP110.6, R43.1, U22.23
SCL22: JP115.6, R45.1, U23.23
SCL23: JP120.6, R47.1, U24.23
SCL24: JP125.6, R49.1, U25.23
SCL25: JP130.6, R51.1, U26.23
SCL26: JP135.6, R53.1, U27.23
SCL27: JP140.6, R55.1, U28.23
SCL28: JP145.6, R57.1, U29.23
SCL29: JP150.6, R59.1, U30.23
SCL30: JP155.6, R61.1, U31.23
SCL31: JP160.6, R63.1, U32.23
SCL32: JP165.6, R65.1, U33.23
SCL33: JP170.6, R67.1, U34.23
SCL34: JP175.6, R69.1, U35.23
SCL35: JP180.6, R71.1, U36.23
SCL36: JP185.6, R73.1, U37.23
SCL37: JP190.6, R75.1, U38.23
SCL38: JP195.6, R77.1, U39.23
SCL39: JP200.6, R79.1, U40.23
SCL40: JP205.6, R81.1, U41.23
SCL41: JP210.6, R83.1, U42.23
SCL42: JP215.6, R85.1, U43.23
SCL43: JP220.6, R87.1, U44.23
SCL44: JP225.6, R89.1, U45.23
SCL45: JP230.6, R91.1, U46.23
SCL46: JP235.6, R93.1, U47.23
SCL47: JP240.6, R95.1, U48.23
SDA: JP6.5, R2.1, U1.24
SDA1: JP10.5, R4.1, U2.24
SDA2: JP15.5, R6.1, U3.24
SDA3: JP20.5, R8.1, U4.24
SDA4: JP25.5, R10.1, U5.24
SDA5: JP30.5, R12.1, U6.24
SDA6: JP35.5, R14.1, U7.24
SDA7: JP40.5, R16.1, U8.24
SDA8: JP45.5, R18.1, U9.24
SDA9: JP50.5, R20.1, U10.24
SDA10: JP55.5, R22.1, U11.24
SDA11: JP60.5, R24.1, U12.24
SDA12: JP65.5, R26.1, U13.24
SDA13: JP70.5, R28.1, U14.24
SDA14: JP75.5, R30.1, U15.24
SDA15: JP80.5, R32.1, U16.24
SDA16: JP85.5, R34.1, U17.24
SDA17: JP90.5, R36.1, U18.24
SDA18: JP95.5, R38.1, U19.24
SDA19: JP100.5, R40.1, U20.24
SDA20: JP105.5, R42.1, U21.24
SDA21: JP110.5, R44.1, U22.24
SDA22: JP115.5, R46.1, U23.24
SDA23: JP120.5, R48.1, U24.24
SDA24: JP125.5, R50.1, U25.24
SDA25: JP130.5, R52.1, U26.24
SDA26: JP135.5, R54.1, U27.24
SDA27: JP140.5, R56.1, U28.24
SDA28: JP145.5, R58.1, U29.24
SDA29: JP150.5, R60.1, U30.24
SDA30: JP155.5, R62.1, U31.24
SDA31: JP160.5, R64.1, U32.24
SDA32: JP165.5, R66.1, U33.24
SDA33: JP170.5, R68.1, U34.24
SDA34: JP175.5, R70.1, U35.24
SDA35: JP180.5, R72.1, U36.24
SDA36: JP185.5, R74.1, U37.24
SDA37: JP190.5, R76.1, U38.24
SDA38: JP195.5, R78.1, U39.24
SDA39: JP200.5, R80.1, U40.24
SDA40: JP205.5, R82.1, U41.24
SDA41: JP210.5, R84.1, U42.24
SDA42: JP215.5, R86.1, U43.24
SDA43: JP220.5, R88.1, U44.24
SDA44: JP225.5, R90.1, U45.24
SDA45: JP230.5, R92.1, U46.24
SDA46: JP235.5, R94.1, U47.24
SDA47: JP240.5, R96.1, U48.24
VCC: C3.1, JP6.10, R1.2, R2.2, SJ1.1, U1.13
VCC1: C7.1, JP10.10, R3.2, R4.2, SJ4.1, U2.13
VCC2: C11.1, JP15.10, R5.2, R6.2, SJ7.1, U3.13
VCC3: C15.1, JP20.10, R7.2, R8.2, SJ10.1, U4.13
VCC4: C19.1, JP25.10, R9.2, R10.2, SJ13.1, U5.13
VCC5: C23.1, JP30.10, R11.2, R12.2, SJ16.1, U6.13
VCC6: C27.1, JP35.10, R13.2, R14.2, SJ19.1, U7.13
VCC7: C31.1, JP40.10, R15.2, R16.2, SJ22.1, U8.13
VCC8: C35.1, JP45.10, R17.2, R18.2, SJ25.1, U9.13
VCC9: C39.1, JP50.10, R19.2, R20.2, SJ28.1, U10.13
VCC10: C43.1, JP55.10, R21.2, R22.2, SJ31.1, U11.13
VCC11: C47.1, JP60.10, R23.2, R24.2, SJ34.1, U12.13
VCC12: C51.1, JP65.10, R25.2, R26.2, SJ37.1, U13.13
VCC13: C55.1, JP70.10, R27.2, R28.2, SJ40.1, U14.13
VCC14: C59.1, JP75.10, R29.2, R30.2, SJ43.1, U15.13
VCC15: C63.1, JP80.10, R31.2, R32.2, SJ46.1, U16.13
VCC16: C67.1, JP85.10, R33.2, R34.2, SJ49.1, U17.13
VCC17: C71.1, JP90.10, R35.2, R36.2, SJ52.1, U18.13
VCC18: C75.1, JP95.10, R37.2, R38.2, SJ55.1, U19.13
VCC19: C79.1, JP100.10, R39.2, R40.2, SJ58.1, U20.13
VCC20: C83.1, JP105.10, R41.2, R42.2, SJ61.1, U21.13
VCC21: C87.1, JP110.10, R43.2, R44.2, SJ64.1, U22.13
VCC22: C91.1, JP115.10, R45.2, R46.2, SJ67.1, U23.13
VCC23: C95.1, JP120.10, R47.2, R48.2, SJ70.1, U24.13
VCC24: C99.1, JP125.10, R49.2, R50.2, SJ73.1, U25.13
VCC25: C103.1, JP130.10, R51.2, R52.2, SJ76.1, U26.13
VCC26: C107.1, JP135.10, R53.2, R54.2, SJ79.1, U27.13
VCC27: C111.1, JP140.10, R55.2, R56.2, SJ82.1, U28.13
VCC28: C115.1, JP145.10, R57.2, R58.2, SJ85.1, U29.13
VCC29: C119.1, JP150.10, R59.2, R60.2, SJ88.1, U30.13
VCC30: C123.1, JP155.10, R61.2, R62.2, SJ91.1, U31.13
VCC31: C127.1, JP160.10, R63.2, R64.2, SJ94.1, U32.13
VCC32: C131.1, JP165.10, R65.2, R66.2, SJ97.1, U33.13
VCC33: C135.1, JP170.10, R67.2, R68.2, SJ100.1, U34.13
VCC34: C139.1, JP175.10, R69.2, R70.2, SJ103.1, U35.13
VCC35: C143.1, JP180.10, R71.2, R72.2, SJ106.1, U36.13
VCC36: C147.1, JP185.10, R73.2, R74.2, SJ109.1, U37.13
VCC37: C151.1, JP190.10, R75.2, R76.2, SJ112.1, U38.13
VCC38: C155.1, JP195.10, R77.2, R78.2, SJ115.1, U39.13
VCC39: C159.1, JP200.10, R79.2, R80.2, SJ118.1, U40.13
VCC40: C163.1, JP205.10, R81.2, R82.2, SJ121.1, U41.13
VCC41: C167.1, JP210.10, R83.2, R84.2, SJ124.1, U42.13
VCC42: C171.1, JP215.10, R85.2, R86.2, SJ127.1, U43.13
VCC43: C175.1, JP220.10, R87.2, R88.2, SJ130.1, U44.13
VCC44: C179.1, JP225.10, R89.2, R90.2, SJ133.1, U45.13
VCC45: C183.1, JP230.10, R91.2, R92.2, SJ136.1, U46.13
VCC46: C187.1, JP235.10, R93.2, R94.2, SJ139.1, U47.13
VCC47: C191.1, JP240.10, R95.2, R96.2, SJ142.1, U48.13
VIO: C4.1, JP6.4, U1.8
VIO1: C8.1, JP10.4, U2.8
VIO2: C12.1, JP15.4, U3.8
VIO3: C16.1, JP20.4, U4.8
VIO4: C20.1, JP25.4, U5.8
VIO5: C24.1, JP30.4, U6.8
VIO6: C28.1, JP35.4, U7.8
VIO7: C32.1, JP40.4, U8.8
VIO8: C36.1, JP45.4, U9.8
VIO9: C40.1, JP50.4, U10.8
VIO10: C44.1, JP55.4, U11.8
VIO11: C48.1, JP60.4, U12.8
VIO12: C52.1, JP65.4, U13.8
VIO13: C56.1, JP70.4, U14.8
VIO14: C60.1, JP75.4, U15.8
VIO15: C64.1, JP80.4, U16.8
VIO16: C68.1, JP85.4, U17.8
VIO17: C72.1, JP90.4, U18.8
VIO18: C76.1, JP95.4, U19.8
VIO19: C80.1, JP100.4, U20.8
VIO20: C84.1, JP105.4, U21.8
VIO21: C88.1, JP110.4, U22.8
VIO22: C92.1, JP115.4, U23.8
VIO23: C96.1, JP120.4, U24.8
VIO24: C100.1, JP125.4, U25.8
VIO25: C104.1, JP130.4, U26.8
VIO26: C108.1, JP135.4, U27.8
VIO27: C112.1, JP140.4, U28.8
VIO28: C116.1, JP145.4, U29.8
VIO29: C120.1, JP150.4, U30.8
VIO30: C124.1, JP155.4, U31.8
VIO31: C128.1, JP160.4, U32.8
VIO32: C132.1, JP165.4, U33.8
VIO33: C136.1, JP170.4, U34.8
VIO34: C140.1, JP175.4, U35.8
VIO35: C144.1, JP180.4, U36.8
VIO36: C148.1, JP185.4, U37.8
VIO37: C152.1, JP190.4, U38.8
VIO38: C156.1, JP195.4, U39.8
VIO39: C160.1, JP200.4, U40.8
VIO40: C164.1, JP205.4, U41.8
VIO41: C168.1, JP210.4, U42.8
VIO42: C172.1, JP215.4, U43.8
VIO43: C176.1, JP220.4, U44.8
VIO44: C180.1, JP225.4, U45.8
VIO45: C184.1, JP230.4, U46.8
VIO46: C188.1, JP235.4, U47.8
VIO47: C192.1, JP240.4, U48.8

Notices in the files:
parts and their libraries:
SparkFun-Aesthetics: Licensing: CC v3.0 Share-Alike You are welcome to use this library for commercial purposes.
SparkFun-Aesthetics: Released under the Creative Commons Attribution Share-Alike 3.0 License
SparkFun-Aesthetics: Released under the Creative Commons
